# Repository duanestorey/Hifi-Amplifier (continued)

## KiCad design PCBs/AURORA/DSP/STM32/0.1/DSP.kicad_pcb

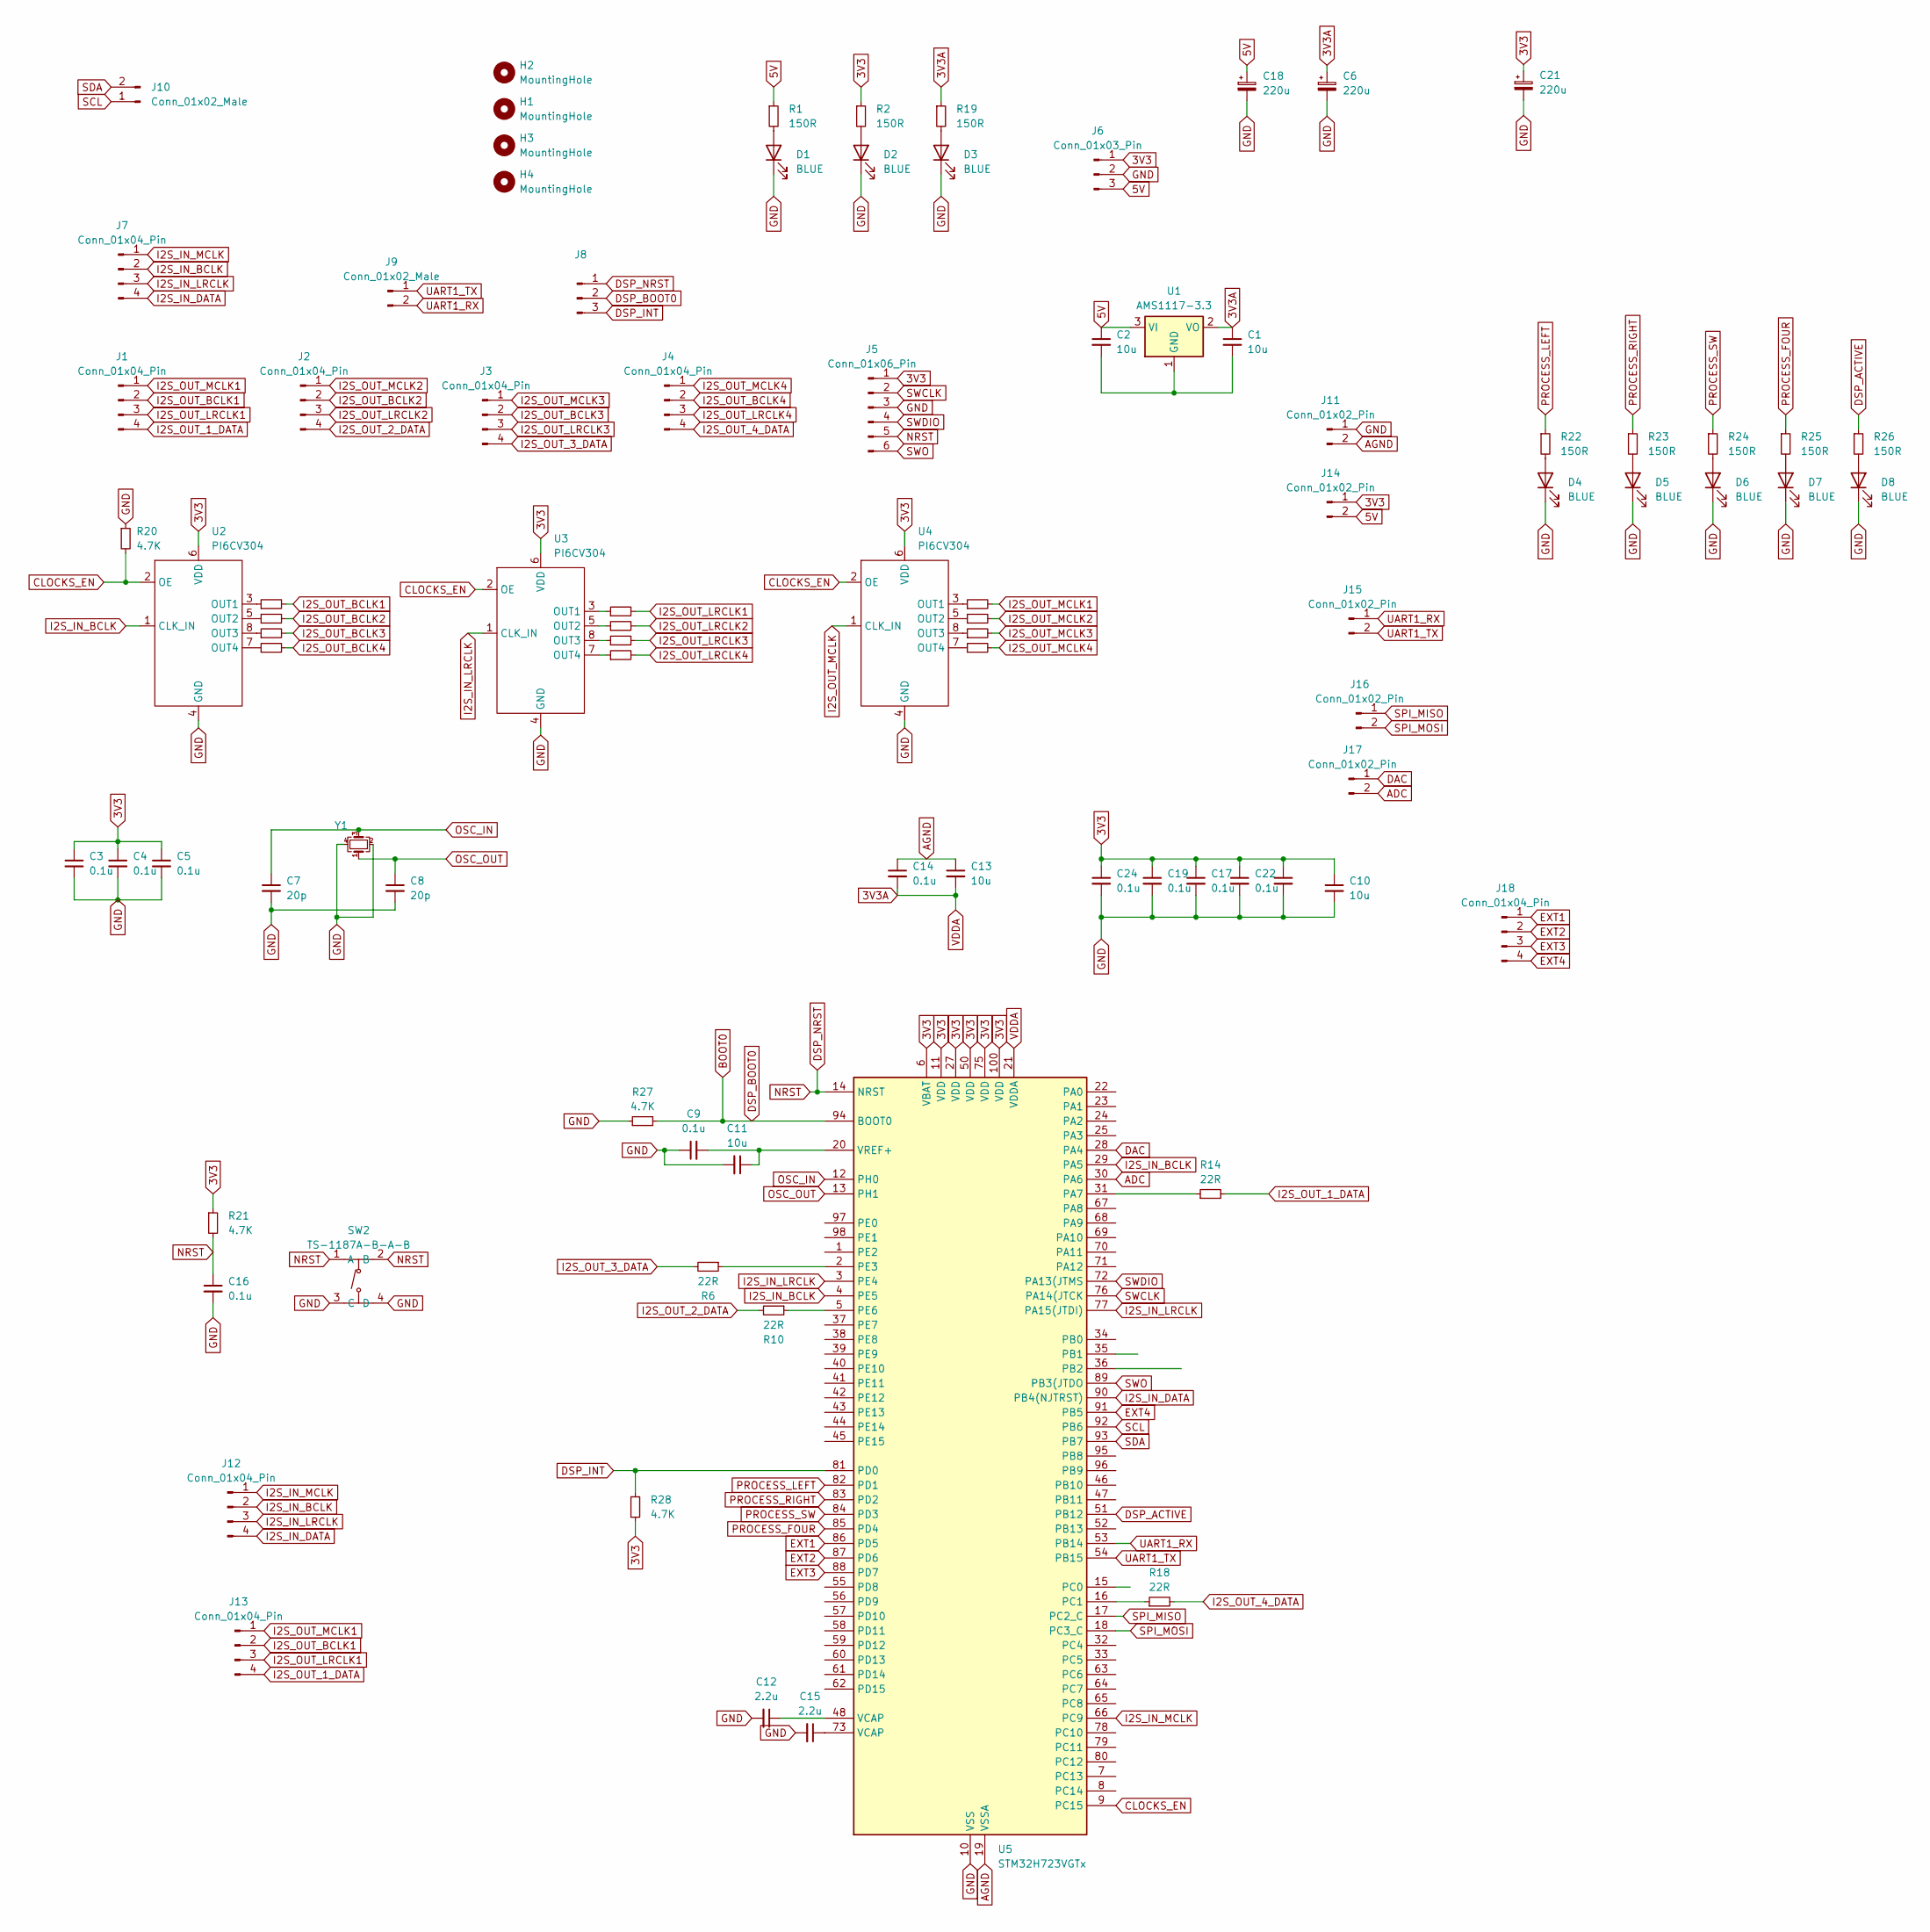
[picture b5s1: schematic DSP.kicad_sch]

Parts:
C1, C2, C10, C11, C13: 10u; C_1206_3216Metric; LCSC C13585
C3, C4, C5, C9, C14, C16, C17, C19, C22, C24, C29: 0.1u; C_0805_2012Metric; LCSC C28233
C6, C18, C21: 220u; CP_Elec_6.3x7.7; LCSC C4747974
C7, C8: 20p; C_0805_2012Metric; LCSC C1798
C12, C15: 2.2u; C_1206_3216Metric; LCSC C50254
D1, D2, D3, D4, D5, D6, D7, D8: BLUE; D_0805_2012Metric; LCSC C84259
H1, H2, H3, H4: MountingHole; MountingHole_3.2mm_M3_DIN965_Pad_TopOnly
J1, J2, J3, J4, J7: Conn_01x04_Pin; JST_PH_B4B-PH-K_1x04_P2.00mm_Vertical
J5: Conn_01x06_Pin; PinHeader_1x06_P2.54mm_Vertical; LCSC C6332199
J6, J8: Conn_01x03_Pin; JST_PH_B3B-PH-K_1x03_P2.00mm_Vertical
J9, J10: Conn_01x02_Male; JST_PH_B2B-PH-K_1x02_P2.00mm_Vertical
J11, J14, J15, J16, J17: Conn_01x02_Pin; PinHeader_1x02_P2.54mm_Vertical; LCSC C225477
J12, J13, J18: Conn_01x04_Pin; PinHeader_1x04_P2.54mm_Vertical; LCSC C6332197
R1, R2, R19, R22, R23, R24, R25, R26: 150R; R_0603_1608Metric; LCSC C22808
R3, R4, R5, R6, R7, R8, R9, R10, R11, R12, R13, R14, R15, R16, R17, R18: 22R; R_0603_1608Metric; LCSC C23345
R20, R21, R27, R28: 4.7K; R_0603_1608Metric; LCSC C23162
SW2: TS-1187A-B-A-B; SW-SMD_4P-L5.1-W5.1-P3.70-LS6.5-TL_H1.5; LCSC Part C318884
U1: AMS1117-3.3; SOT-223-3_TabPin2; LCSC C6186
U2, U3, U4: PI6CV304; TSSOP-8_4.4x3mm_P0.65mm; Mouser 729-PI6CV304LEX
U5: STM32H723VGTx; LQFP-100_14x14mm_P0.5mm; LCSC C730142
Y1: 25 MHz; Crystal_SMD_SeikoEpson_FA238-4Pin_3.2x2.5mm; Mouser 520-240-8-33B2CKMTR3

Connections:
3V3: C3.1, C4.1, C5.1, C10.1, C17.1, C19.1, C21.1, C22.1, C24.1, C29.1, J5.1, J6.1, J14.1, R2.1, R21.1, R28.2, U2.6 (VDD), U3.6 (VDD), U4.6 (VDD), U5.6 (VBAT), U5.11 (VDD), U5.27 (VDD), U5.50 (VDD), U5.75 (VDD), U5.100 (VDD)
3V3A: C1.1, C6.1, C13.2, C14.2, R19.1, U1.2 (VO), U5.21 (VDDA)
5V: C2.1, C18.1, J6.3, J14.2, R1.1, U1.3 (VI)
ADC: J17.2, U5.30 (PA6)
AGND: C13.1, C14.1, J11.2, U5.19 (VSSA)
BOOT0: J8.2, R27.2, U5.94 (BOOT0)
CLOCKS_EN: R20.2, U2.2 (OE), U3.2 (OE), U4.2 (OE), U5.9 (PC15)
DAC: J17.1, U5.28 (PA4)
DSP_ACTIVE: R26.1, U5.51 (PB12)
DSP_INT: J8.3, R28.1, U5.81 (PD0)
DSP_NRST: C16.1, J5.5, J8.1, R21.2, SW2.1 (A), SW2.2 (B), U5.14 (NRST)
EXT1: J18.1, U5.86 (PD5)
EXT2: J18.2, U5.87 (PD6)
EXT3: J18.3, U5.88 (PD7)
EXT4: J18.4, U5.91 (PB5)
GND: C3.2, C4.2, C5.2, C6.2, C7.2, C8.2, C9.1, C10.2, C11.2, C12.2, C15.2, C16.2, C17.2, C18.2, C19.2, C21.2, C22.2, C24.2, C29.2, D1.1 (K), D2.1 (K), D3.1 (K), D4.1 (K), D5.1 (K), D6.1 (K), D7.1 (K), D8.1 (K), J5.3, J6.2, J11.1, R20.1, R27.1, SW2.3 (C), SW2.4 (D), U2.4 (GND), U3.4 (GND), U4.4 (GND), U5.10 (VSS), U5.26 (VSS), U5.49 (VSS), U5.74 (VSS), U5.99 (VSS), Y1.2, Y1.4
I2S_IN_BCLK: J7.2, J12.2, U2.1 (CLK_IN), U5.4 (PE5), U5.29 (PA5)
I2S_IN_DATA: J7.4, J12.4, U5.90 (PB4(NJTRST))
I2S_IN_LRCLK: J7.3, J12.3, U3.1 (CLK_IN), U5.3 (PE4), U5.77 (PA15(JTDI))
I2S_IN_MCLK: J7.1, J12.1, U5.66 (PC9)
I2S_OUT_1_DATA: J1.4, J13.4, R14.2
I2S_OUT_2_DATA: J2.4, R10.2
I2S_OUT_3_DATA: J3.4, R6.2
I2S_OUT_4_DATA: J4.4, R18.2
I2S_OUT_BCLK1: J1.2, J13.2, R4.2
I2S_OUT_BCLK2: J2.2, R8.2
I2S_OUT_BCLK3: J3.2, R12.2
I2S_OUT_BCLK4: J4.2, R16.2
I2S_OUT_LRCLK1: J1.3, J13.3, R5.2
I2S_OUT_LRCLK2: J2.3, R9.2
I2S_OUT_LRCLK3: J3.3, R13.2
I2S_OUT_LRCLK4: J4.3, R17.2
I2S_OUT_MCLK: U4.1 (CLK_IN)
I2S_OUT_MCLK1: J1.1, J13.1, R3.2
I2S_OUT_MCLK2: J2.1, R7.2
I2S_OUT_MCLK3: J3.1, R11.2
I2S_OUT_MCLK4: J4.1, R15.2
unnamed: C12.1, U5.48 (VCAP)
unnamed: C15.1, U5.73 (VCAP)
unnamed: D1.2 (A), R1.2
unnamed: D2.2 (A), R2.2
unnamed: D3.2 (A), R19.2
unnamed: D4.2 (A), R22.2
unnamed: D5.2 (A), R23.2
unnamed: D6.2 (A), R24.2
unnamed: D7.2 (A), R25.2
unnamed: D8.2 (A), R26.2
unnamed: C1.2, C2.2, U1.1 (GND)
unnamed: R4.1, U2.3 (OUT1)
unnamed: R8.1, U2.5 (OUT2)
unnamed: R12.1, U2.8 (OUT3)
unnamed: R16.1, U2.7 (OUT4)
unnamed: R5.1, U3.3 (OUT1)
unnamed: R9.1, U3.5 (OUT2)
unnamed: R13.1, U3.8 (OUT3)
unnamed: R17.1, U3.7 (OUT4)
unnamed: R3.1, U4.3 (OUT1)
unnamed: R7.1, U4.5 (OUT2)
unnamed: R11.1, U4.8 (OUT3)
unnamed: R15.1, U4.7 (OUT4)
unnamed: R14.1, U5.31 (PA7)
unnamed: R18.1, U5.16 (PC1)
unnamed: R6.1, U5.2 (PE3)
unnamed: R10.1, U5.5 (PE6)
unnamed: C9.2, C11.1, U5.20 (VREF+)
OSC_IN: C7.1, U5.12 (PH0), Y1.3
OSC_OUT: C8.1, U5.13 (PH1), Y1.1
PROCESS_FOUR: R25.1, U5.85 (PD4)
PROCESS_LEFT: R22.1, U5.82 (PD1)
PROCESS_RIGHT: R23.1, U5.83 (PD2)
PROCESS_SW: R24.1, U5.84 (PD3)
SCL: J10.1, U5.92 (PB6)
SDA: J10.2, U5.93 (PB7)
SPI_MISO: J16.1, U5.17 (PC2_C)
SPI_MOSI: J16.2, U5.18 (PC3_C)
SWCLK: J5.2, U5.76 (PA14(JTCK)
SWDIO: J5.4, U5.72 (PA13(JTMS)
SWO: J5.6, U5.89 (PB3(JTDO)
UART1_RX: J9.2, J15.1, U5.53 (PB14)
UART1_TX: J9.1, J15.2, U5.54 (PB15)

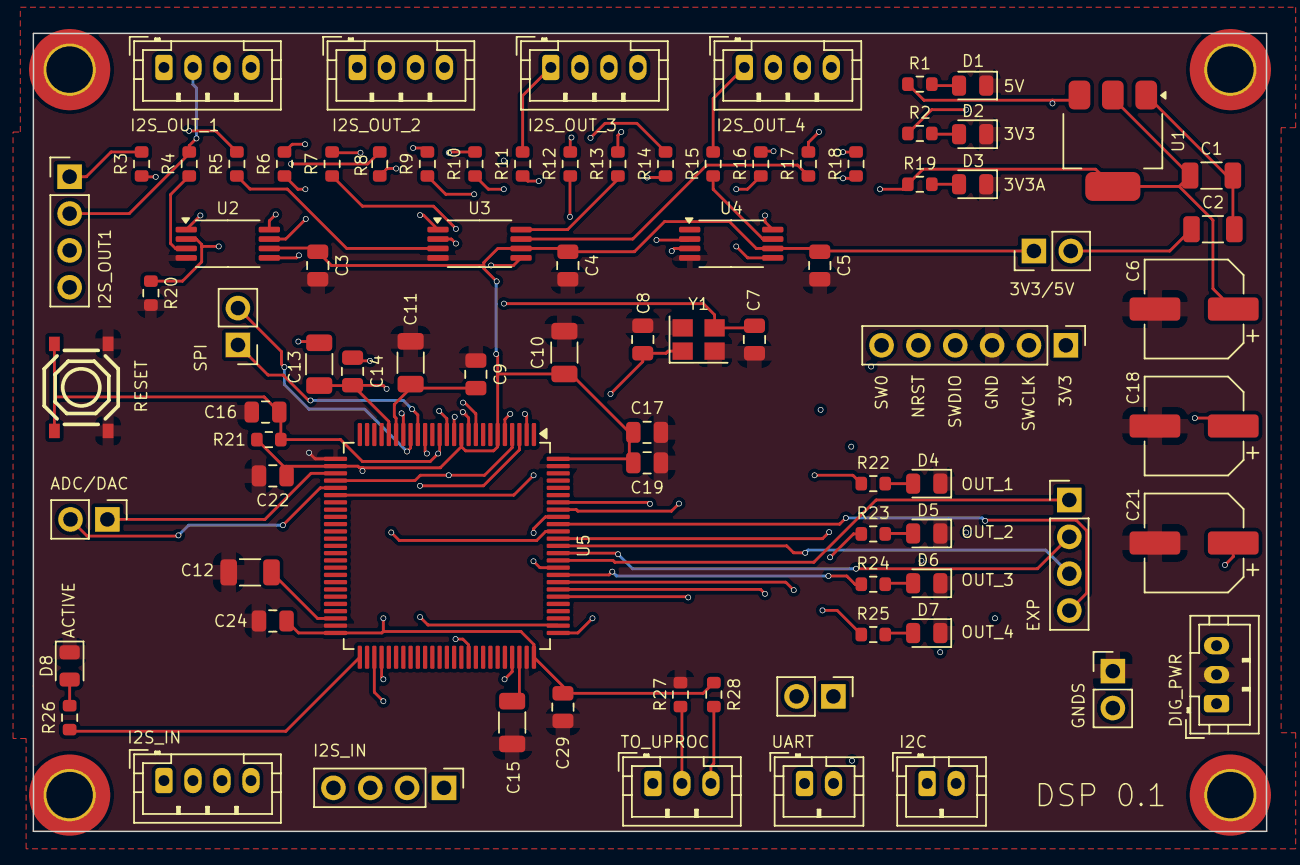
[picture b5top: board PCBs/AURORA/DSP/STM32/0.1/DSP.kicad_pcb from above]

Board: 4 copper layers, 85.0 x 55.0 mm, 88 parts (0 on the bottom side), 79 nets.

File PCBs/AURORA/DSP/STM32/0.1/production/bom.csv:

Designator,Footprint,Quantity,Value,LCSC Part #
"C1, C10, C11, C13, C2",1206,5,10u,C13585
"C12, C15",1206,2,2.2u,C50254
"C14, C16, C17, C19, C22, C24, C29, C3, C4, C5, C9",0805,11,0.1u,C28233
"C18, C21, C6",CP_Elec_6.3x7.7,3,220u,C4747974
"C7, C8",0805,2,20p,C1798
"D1, D2, D3, D4, D5, D6, D7, D8",0805,8,BLUE,C84259
"J1, J2, J3, J4, J7",JST_PH_B4B-PH-K_1x04_P2.00mm_Vertical,5,Conn_01x04_Pin,
"J10, J9",JST_PH_B2B-PH-K_1x02_P2.00mm_Vertical,2,Conn_01x02_Male,
"J11, J14, J15, J16, J17",PinHeader_1x02_P2.54mm_Vertical,5,Conn_01x02_Pin,C225477
"J12, J13, J18",PinHeader_1x04_P2.54mm_Vertical,3,Conn_01x04_Pin,C6332197
J5,PinHeader_1x06_P2.54mm_Vertical,1,Conn_01x06_Pin,C6332199
"J6, J8",JST_PH_B3B-PH-K_1x03_P2.00mm_Vertical,2,Conn_01x03_Pin,
"R1, R19, R2, R22, R23, R24, R25, R26",0603,8,150R,C22808
"R10, R11, R12, R13, R14, R15, R16, R17, R18, R3, R4, R5, R6, R7, R8, R9",0603,16,22R,C23345
"R20, R21, R27, R28",0603,4,4.7K,C23162
SW2,SW-SMD_4P-L5.1-W5.1-P3.70-LS6.5-TL_H1.5,1,TS-1187A-B-A-B,C318884
U1,SOT-223-3_TabPin2,1,AMS1117-3.3,C6186
"U2, U3, U4",TSSOP-8_4.4x3mm_P0.65mm,3,PI6CV304,C2649345
U5,LQFP-100_14x14mm_P0.5mm,1,STM32H723VGTx,C730142
Y1,Crystal_SMD_SeikoEpson_FA238-4Pin_3.2x2.5mm,1,25 MHz,C9006

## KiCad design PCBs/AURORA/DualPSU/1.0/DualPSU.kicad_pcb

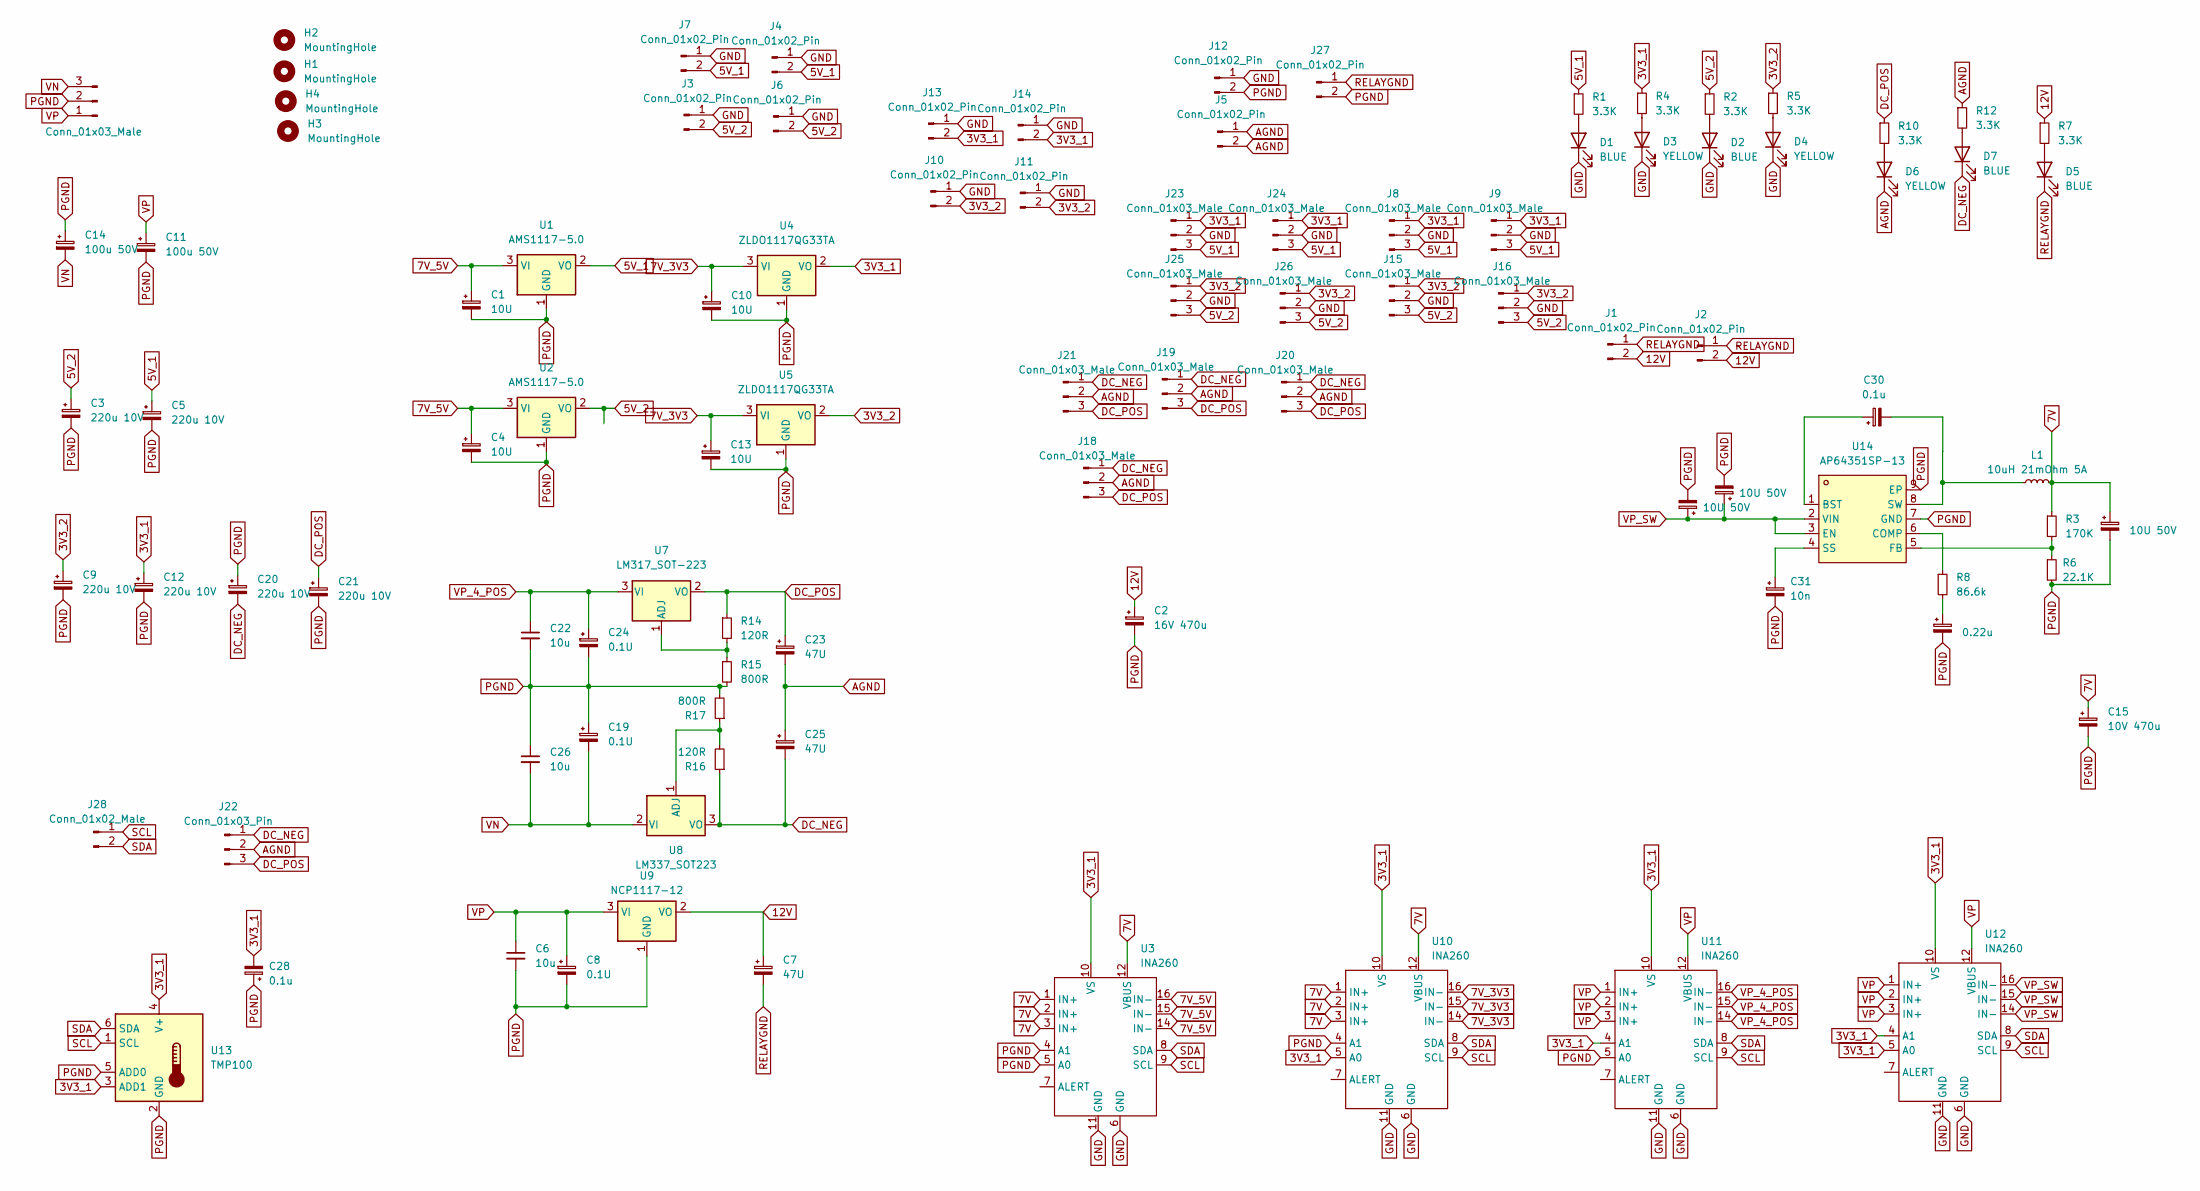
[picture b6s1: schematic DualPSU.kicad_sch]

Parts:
C1, C4, C10, C13: 10U; C_1206_3216Metric_Pad1.33x1.80mm_HandSolder
C2: 16V 470u; CP_Radial_D8.0mm_P3.50mm
C3, C5, C9, C12, C20, C21: 220u 10V; CP_Radial_D6.3mm_P2.50mm
C6, C22, C26: 10u; C_1206_3216Metric_Pad1.33x1.80mm_HandSolder
C7, C23, C25: 47U; C_1206_3216Metric_Pad1.33x1.80mm_HandSolder
C8, C19, C24: 0.1U; C_0603_1608Metric_Pad1.08x0.95mm_HandSolder
C11, C14: 100u 50V; CP_Radial_D8.0mm_P3.50mm
C15: 10V 470u; CP_Radial_D8.0mm_P3.50mm
C16, C18, C29: 10U 50V; C_1206_3216Metric_Pad1.33x1.80mm_HandSolder
C27: 0.22u; C_0805_2012Metric_Pad1.18x1.45mm_HandSolder
C28, C30: 0.1u; C_0805_2012Metric_Pad1.18x1.45mm_HandSolder
C31: 10n; C_0805_2012Metric_Pad1.18x1.45mm_HandSolder
D1, D2, D5, D7: BLUE; LED_0805_2012Metric_Pad1.15x1.40mm_HandSolder
D3, D4, D6: YELLOW; LED_0805_2012Metric_Pad1.15x1.40mm_HandSolder
H1, H2, H3, H4: MountingHole; MountingHole_3.2mm_M3_DIN965_Pad_TopOnly
J1, J2, J3, J4, J5, J6, J7, J10, J11, J13, J14: Conn_01x02_Pin; JST_PH_B2B-PH-K_1x02_P2.00mm_Vertical
J8, J9, J15, J16, J18, J19, J20, J21, J23, J24, J25, J26: Conn_01x03_Male; JST_PH_B3B-PH-K_1x03_P2.00mm_Vertical
J12, J27: Conn_01x02_Pin; PinHeader_1x02_P2.54mm_Vertical
J17: Conn_01x03_Male; JST_VH_B3P-VH_1x03_P3.96mm_Vertical
J22: Conn_01x03_Pin; PinHeader_1x03_P2.54mm_Vertical
J28: Conn_01x02_Male; JST_PH_B2B-PH-K_1x02_P2.00mm_Vertical
L1: 10uH 21mOhm 5A; L_Vishay_IHLP-4040; Mouser 704-DR1040-7R0-R
R1, R2, R4, R5, R7, R10, R12: 3.3K; R_0603_1608Metric_Pad0.98x0.95mm_HandSolder
R3: 170K; R_0603_1608Metric_Pad0.98x0.95mm_HandSolder
R6: 22.1K; R_0603_1608Metric_Pad0.98x0.95mm_HandSolder; Mouser 603-RC0603JR-07820KP
R8: 86.6k; R_0603_1608Metric_Pad0.98x0.95mm_HandSolder; Mouser 71-CRCW0603-86.6K-E3
R14, R16: 120R; R_0603_1608Metric_Pad0.98x0.95mm_HandSolder
R15, R17: 800R; R_0603_1608Metric_Pad0.98x0.95mm_HandSolder
U1, U2: AMS1117-5.0; SOT-223-3_TabPin2; Mouser 926-LM1117MPX5.0NOPB
U3, U10, U11, U12: INA260; TSSOP-16_4.4x5mm_P0.65mm
U4, U5: ZLDO1117QG33TA; SOT-223-3_TabPin2; Mouser ZLDO1117QG33TA
U7: LM317_SOT-223; SOT-223-3_TabPin2; Mouser 595-LM317DCY
U8: LM337_SOT223; SOT-223-3_TabPin2; Mouser 926-LM337IMPX/NOPB
U9: NCP1117-12; SOT-223; Mouser 863-NCP1117ST12T3G
U13: TMP100; SOT-23-6; Mouser 595-TMP100NA/3K
U14: AP64351SP-13; SOIC-8_L4.9-W3.9-P1.27-LS6.0-BL-EP; LCSC Part C3192339

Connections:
3V3_1: C12.1, C28.2, J8.1, J9.1, J13.2, J14.2, J23.1, J24.1, R4.1, U3.10 (VS), U4.2 (VO), U10.5 (A0), U10.10 (VS), U11.4 (A1), U11.10 (VS), U12.4 (A1), U12.5 (A0), U12.10 (VS), U13.3 (ADD1), U13.4 (V+)
3V3_2: C9.1, J10.2, J11.2, J15.1, J16.1, J25.1, J26.1, R5.1, U5.2 (VO)
5V_1: C5.1, J4.2, J7.2, J8.3, J9.3, J23.3, J24.3, R1.1, U1.2 (VO)
5V_2: C3.1, J3.2, J6.2, J15.3, J16.3, J25.3, J26.3, R2.1, U2.2 (VO)
7V: C15.1, C18.1, L1.2, R3.1, U3.1 (IN+), U3.2 (IN+), U3.3 (IN+), U3.12 (VBUS), U10.1 (IN+), U10.2 (IN+), U10.3 (IN+), U10.12 (VBUS)
7V_3V3: C10.1, C13.1, U4.3 (VI), U5.3 (VI), U10.14 (IN-), U10.15 (IN-), U10.16 (IN-)
7V_5V: C1.1, C4.1, U1.3 (VI), U2.3 (VI), U3.14 (IN-), U3.15 (IN-), U3.16 (IN-)
12V: C2.1, C7.1, J1.2, J2.2, R7.1, U9.2 (VO)
AGND: C23.2, C25.1, D6.1 (K), J5.1, J5.2, J18.2, J19.2, J20.2, J21.2, J22.2, R12.1
DC_NEG: C20.2, C25.2, D7.1 (K), J18.1, J19.1, J20.1, J21.1, J22.1, R16.1, U8.3 (VO)
DC_POS: C21.1, C23.1, J18.3, J19.3, J20.3, J21.3, J22.3, R10.1, R14.1, U7.2 (VO)
GND: D1.1 (K), D2.1 (K), D3.1 (K), D4.1 (K), J3.1, J4.1, J6.1, J7.1, J8.2, J9.2, J10.1, J11.1, J12.1, J13.1, J14.1, J15.2, J16.2, J23.2, J24.2, J25.2, J26.2, U3.6 (GND), U3.11 (GND), U10.6 (GND), U10.11 (GND), U11.6 (GND), U11.11 (GND), U12.6 (GND), U12.11 (GND)
unnamed: C27.1, R8.2
unnamed: D1.2 (A), R1.2
unnamed: D2.2 (A), R2.2
unnamed: D3.2 (A), R4.2
unnamed: D4.2 (A), R5.2
unnamed: D5.2 (A), R7.2
unnamed: D6.2 (A), R10.2
unnamed: D7.2 (A), R12.2
unnamed: R14.2, R15.1, U7.1 (ADJ)
unnamed: R16.2, R17.1, U8.1 (ADJ)
unnamed: C30.1, U14.1 (BST)
unnamed: R8.1, U14.6 (COMP)
unnamed: R3.2, R6.1, U14.5 (FB)
unnamed: C31.1, U14.4 (SS)
unnamed: C30.2, L1.1, U14.8 (SW)
PGND: C1.2, C2.2, C3.2, C4.2, C5.2, C6.2, C8.2, C9.2, C10.2, C11.2, C12.2, C13.2, C14.1, C15.2, C16.2, C18.2, C19.1, C20.1, C21.2, C22.2, C24.2, C26.1, C27.2, C28.1, C29.2, C31.2, J12.2, J17.2, J27.2, R6.2, R15.2, R17.2, U1.1 (GND), U2.1 (GND), U3.4 (A1), U3.5 (A0), U4.1 (GND), U5.1 (GND), U9.1 (GND), U10.4 (A1), U11.5 (A0), U13.2 (GND), U13.5 (ADD0), U14.7 (GND), U14.9 (EP)
RELAYGND: C7.2, D5.1 (K), J1.1, J2.1, J27.1
SCL: J28.1, U3.9 (SCL), U10.9 (SCL), U11.9 (SCL), U12.9 (SCL), U13.1 (SCL)
SDA: J28.2, U3.8 (SDA), U10.8 (SDA), U11.8 (SDA), U12.8 (SDA), U13.6 (SDA)
VN: C14.2, C19.2, C26.2, J17.3, U8.2 (VI)
VP: C6.1, C8.1, C11.1, J17.1, U9.3 (VI), U11.1 (IN+), U11.2 (IN+), U11.3 (IN+), U11.12 (VBUS), U12.1 (IN+), U12.2 (IN+), U12.3 (IN+), U12.12 (VBUS)
VP_4_POS: C22.1, C24.1, U7.3 (VI), U11.14 (IN-), U11.15 (IN-), U11.16 (IN-)
VP_SW: C16.1, C29.1, U12.14 (IN-), U12.15 (IN-), U12.16 (IN-), U14.2 (VIN), U14.3 (EN)

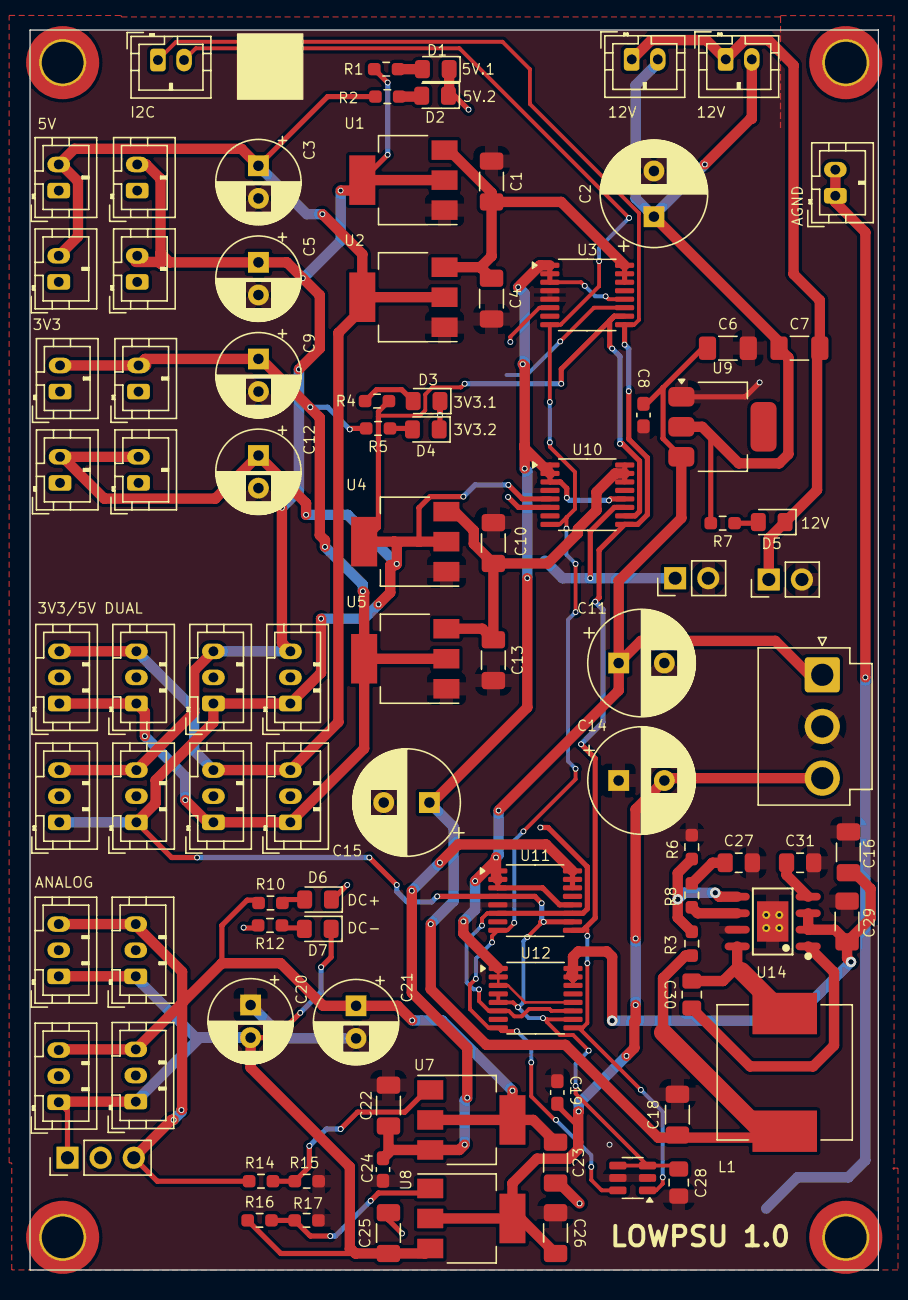
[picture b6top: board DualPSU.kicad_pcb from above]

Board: 2 copper layers, 65.0 x 95.0 mm, 97 parts (0 on the bottom side), 35 nets.
